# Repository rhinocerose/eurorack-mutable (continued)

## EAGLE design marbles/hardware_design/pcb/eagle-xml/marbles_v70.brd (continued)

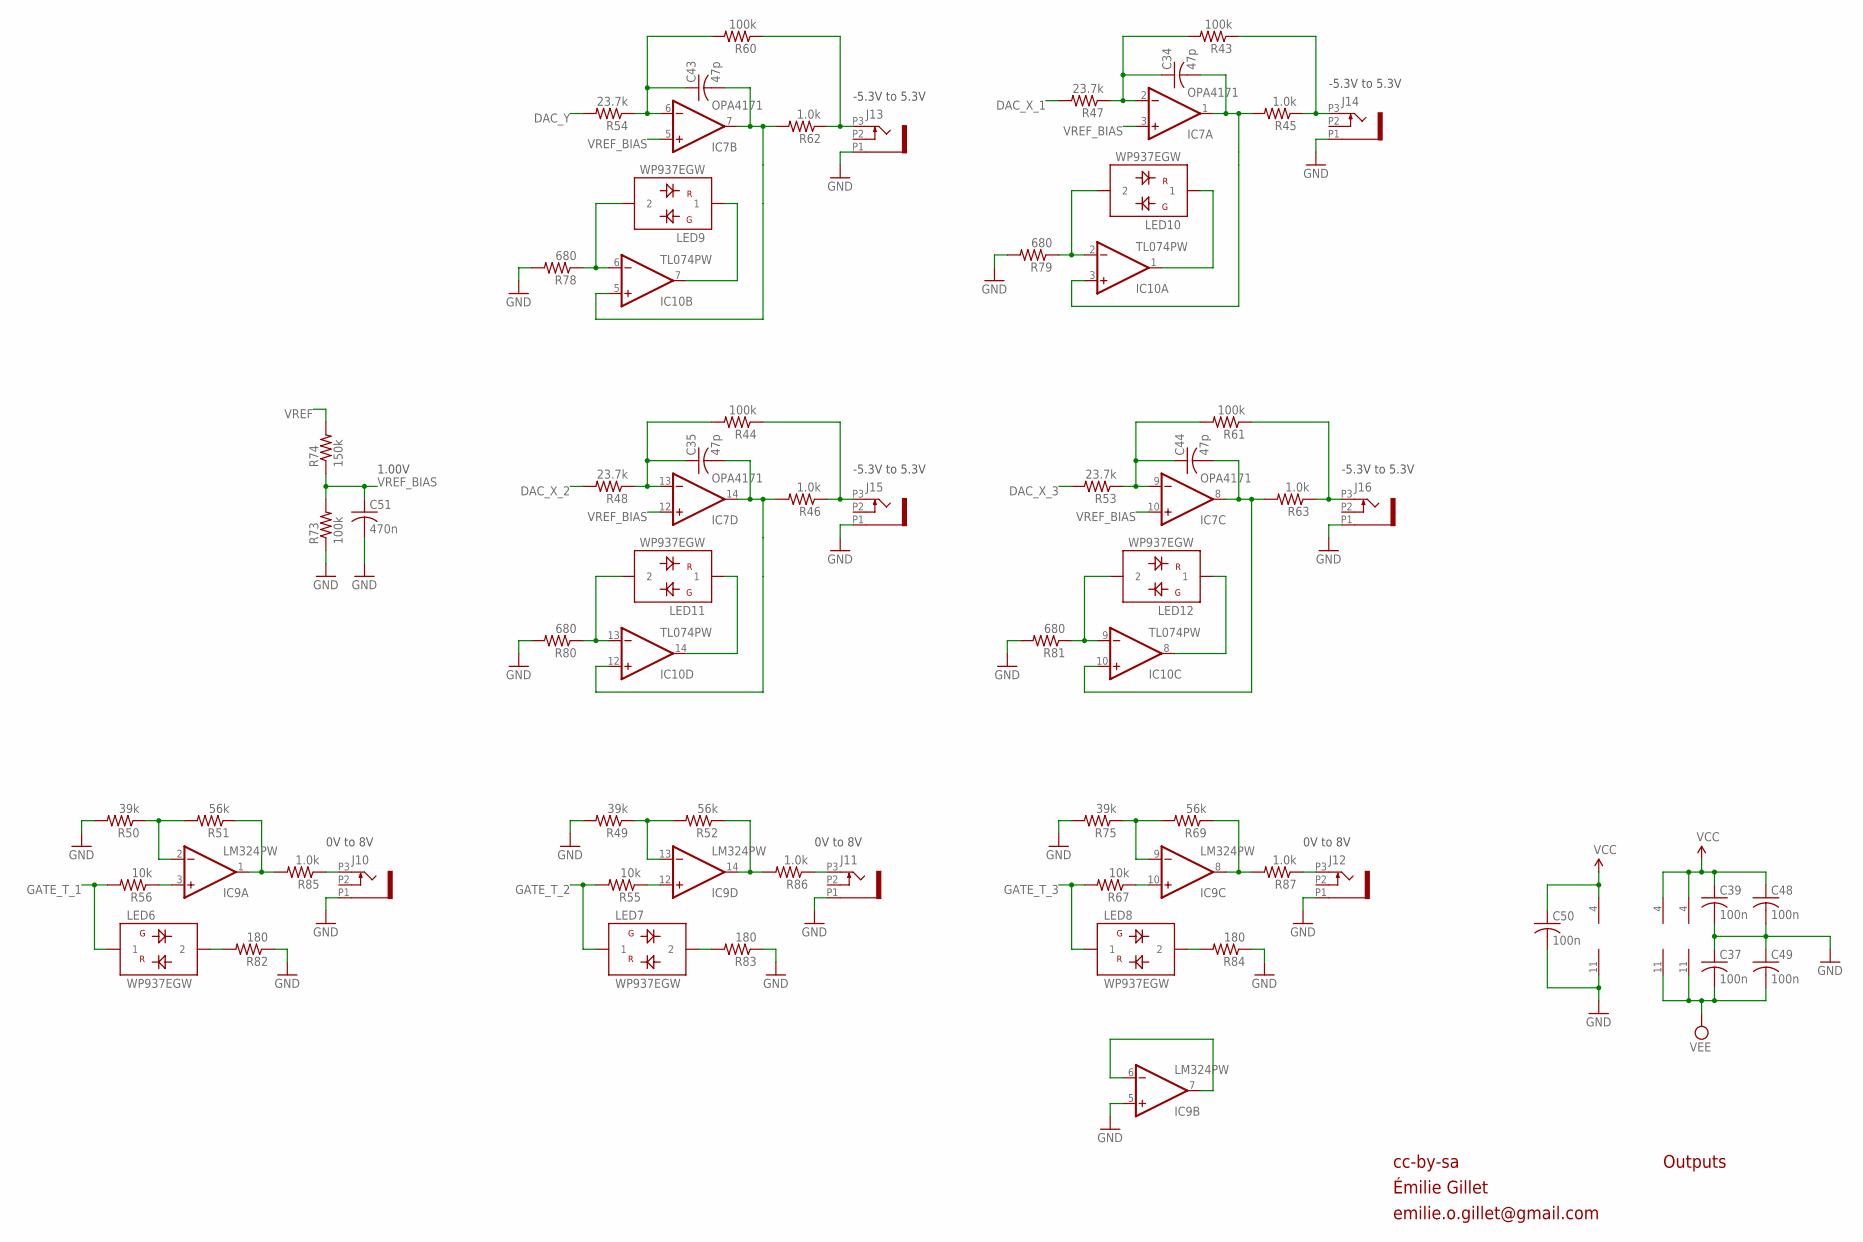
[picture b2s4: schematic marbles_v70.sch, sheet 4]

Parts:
C34, C35, C43, C44: 47p; C0402
C37, C39, C48, C49, C50: 100n; C0402
C51: 470n; C0402
IC7: OPA4171; TSSOP14_065
IC9: LM324PW; TSSOP14_065
IC10: TL074PW; TSSOP14_065
J10, J11, J12, J13, J14, J15, J16: PJ301_THONKICONN6; WQP_PJ_301M6
LED6, LED7, LED8, LED9, LED10, LED11, LED12: WP937EGW; LED3MM
R43, R44, R60, R61, R73: 100k; R0402
R45, R46, R62, R63, R85, R86, R87: 1.0k; R0603
R47, R48, R53, R54: 23.7k; R0402
R49, R50, R75: 39k; R0402
R51, R52, R69: 56k; R0402
R55, R56, R67: 10k; R0402
R74: 150k; R0402
R78, R79, R80, R81: 680; R0402
R82, R83, R84: 180; R0402

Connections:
DAC_X_1: R47.2; also elsewhere on the board
DAC_X_2: R48.2; also elsewhere on the board
DAC_X_3: R53.2; also elsewhere on the board
DAC_Y: R54.2; also elsewhere on the board
GATE_T_1: LED6.1, R56.2; also elsewhere on the board
GATE_T_2: LED7.1, R55.2; also elsewhere on the board
GATE_T_3: LED8.1, R67.2; also elsewhere on the board
GND: C37.1, C39.2, C48.2, C49.1, C50.2, C51.2, IC9.5 (+IN), IC9.11 (V-), J10.P1 (1), J11.P1 (1), J12.P1 (1), J13.P1 (1), J14.P1 (1), J15.P1 (1), J16.P1 (1), R49.2, R50.2, R73.1, R75.2, R78.2, R79.2, R80.2, R81.2, R82.1, R83.1, R84.1; also elsewhere on the board
unnamed: IC9.12 (+IN), R55.1
unnamed: IC9.1 (OUT), R51.1, R85.2
unnamed: J10.P3 (3), R85.1
unnamed: IC9.2 (-IN), R50.1, R51.2
unnamed: LED6.2, R82.2
unnamed: IC9.3 (+IN), R56.1
unnamed: IC9.6 (-IN), IC9.7 (OUT)
unnamed: IC9.14 (OUT), R52.1, R86.2
unnamed: IC9.13 (-IN), R49.1, R52.2
unnamed: IC9.10 (+IN), R67.1
unnamed: IC9.8 (OUT), R69.1, R87.2
unnamed: J11.P3 (3), R86.1
unnamed: J12.P3 (3), R87.1
unnamed: IC9.9 (-IN), R69.2, R75.1
unnamed: LED7.2, R83.2
unnamed: C43.2, IC7.7 (OUT), IC10.5 (+IN), R62.2
unnamed: LED8.2, R84.2
unnamed: J15.P3 (3), R44.1, R46.1
unnamed: J13.P3 (3), R60.1, R62.1
unnamed: C35.1, IC7.13 (-IN), R44.2, R48.1
unnamed: J16.P3 (3), R61.1, R63.1
unnamed: C44.1, IC7.9 (-IN), R53.1, R61.2
unnamed: C34.1, IC7.2 (-IN), R43.2, R47.1
unnamed: C43.1, IC7.6 (-IN), R54.1, R60.2
unnamed: J14.P3 (3), R43.1, R45.1
unnamed: IC10.6 (-IN), LED9.2, R78.1
unnamed: IC10.7 (OUT), LED9.1
unnamed: C34.2, IC7.1 (OUT), IC10.3 (+IN), R45.2
unnamed: IC10.2 (-IN), LED10.2, R79.1
unnamed: IC10.1 (OUT), LED10.1
unnamed: C35.2, IC7.14 (OUT), IC10.12 (+IN), R46.2
unnamed: IC10.13 (-IN), LED11.2, R80.1
unnamed: IC10.14 (OUT), LED11.1
unnamed: C44.2, IC7.8 (OUT), IC10.10 (+IN), R63.2
unnamed: IC10.9 (-IN), LED12.2, R81.1
unnamed: IC10.8 (OUT), LED12.1
VCC: C39.1, C48.1, C50.1, IC7.4 (V+), IC9.4 (V+), IC10.4 (V+); also elsewhere on the board
VEE: C37.2, C49.2, IC7.11 (V-), IC10.11 (V-); also elsewhere on the board
VREF: R74.2; also elsewhere on the board
VREF_BIAS: C51.1, IC7.3 (+IN), IC7.5 (+IN), IC7.10 (+IN), IC7.12 (+IN), R73.2, R74.1

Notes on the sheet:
-5.3V to 5.3V
0V to 8V
cc-by-sa
Outputs
1.00V
Émilie Gillet
emilie.o.gillet@gmail.com

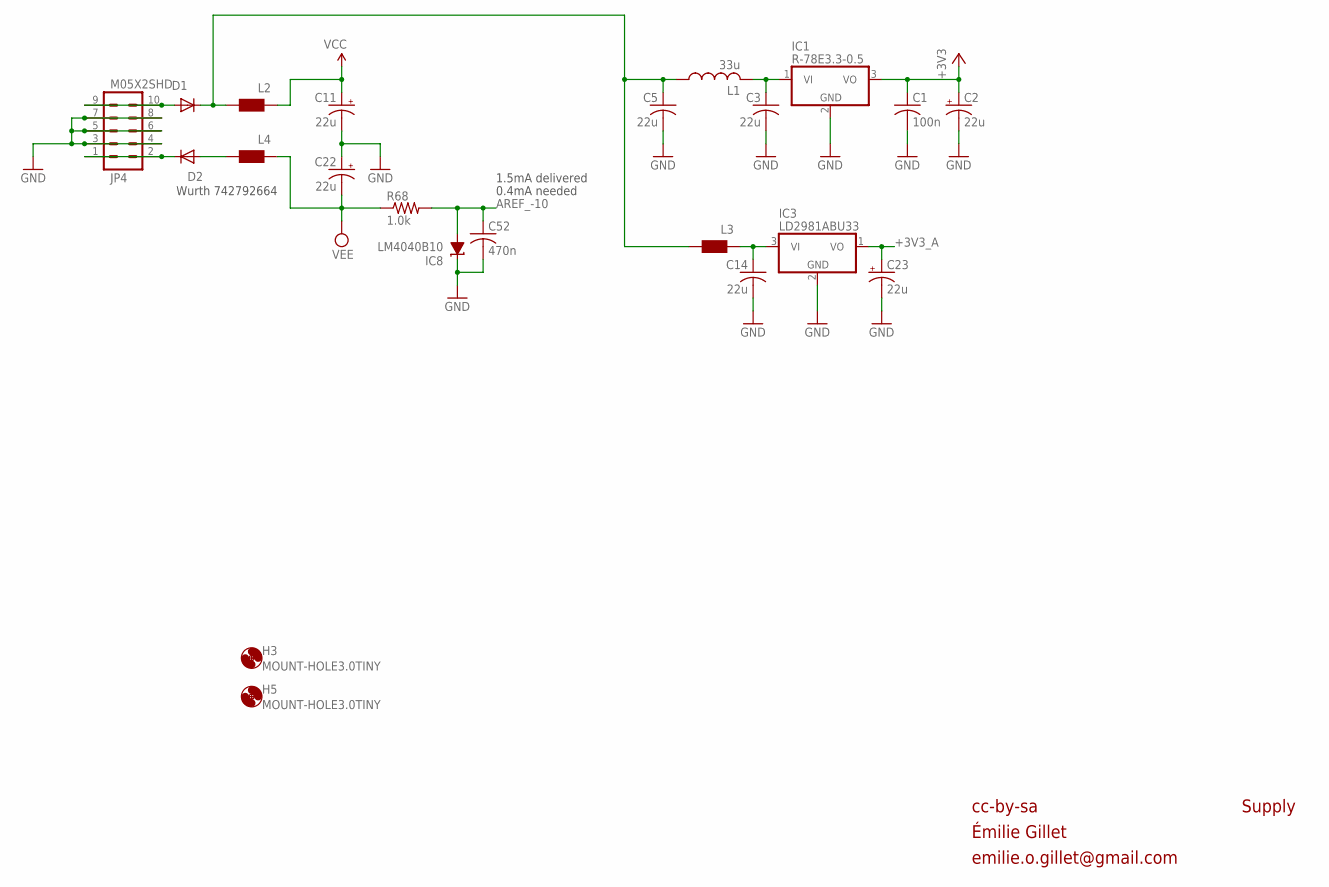
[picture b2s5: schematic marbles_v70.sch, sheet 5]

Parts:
C1: 100n; C0402
C2, C11, C22, C23: 22u; PANASONIC_C
C3, C5, C14: 22u; C1206
C52: 470n; C0402
D1, D2: 1N5819HW; SOD123
H3, H5: MOUNT-HOLE3.0TINY; 3,0TINY
IC1: R-78E3.3-0.5; WE78
IC3: LD2981ABU33; SOT89
IC8: LM4040B10; DBZ_R-PDSO-G3
JP4: M05X2SHD; 2X5-SHROUDED
L1: 33u; L2012C
L2, L3, L4: WE-CBF_0603; 0603
R68: 1.0k; R0402

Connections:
+3V3: C1.1, C2.+, IC1.3 (VO); also elsewhere on the board
+3V3_A: C23.+, IC3.1 (VO); also elsewhere on the board
AREF_-10: C52.1, IC8.2 (A), R68.2; also elsewhere on the board
GND: C1.2, C2.-, C3.2, C5.2, C11.-, C14.2, C22.+, C23.-, C52.2, IC1.2 (GND), IC3.2 (GND), IC8.1 (C), JP4.3, JP4.4, JP4.5, JP4.6, JP4.7, JP4.8; also elsewhere on the board
unnamed: C14.1, IC3.3 (VI), L3.1
unnamed: C5.1, D1.C, L1.1, L2.2, L3.2
unnamed: D2.A, L4.2
unnamed: C3.1, IC1.1 (VI), L1.2
unnamed: D1.A, JP4.9, JP4.10
unnamed: D2.C, JP4.1, JP4.2
VCC: C11.+, L2.1; also elsewhere on the board
VEE: C22.-, L4.1, R68.1; also elsewhere on the board

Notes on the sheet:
0.4mA needed
cc-by-sa
Supply
Wurth 742792664
1.5mA delivered
Émilie Gillet
emilie.o.gillet@gmail.com

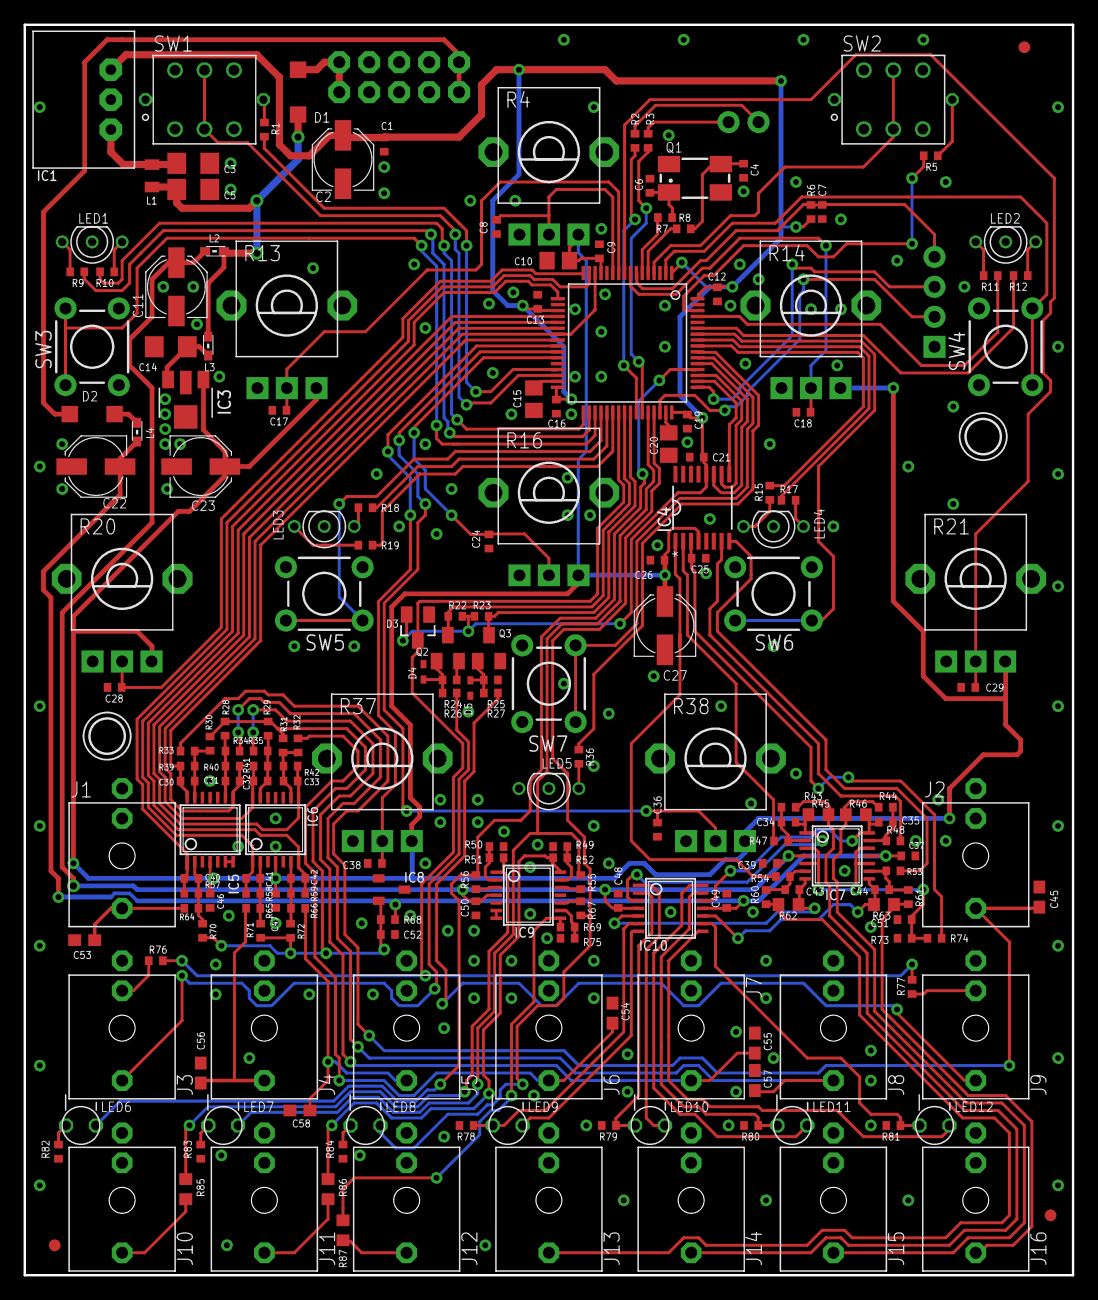
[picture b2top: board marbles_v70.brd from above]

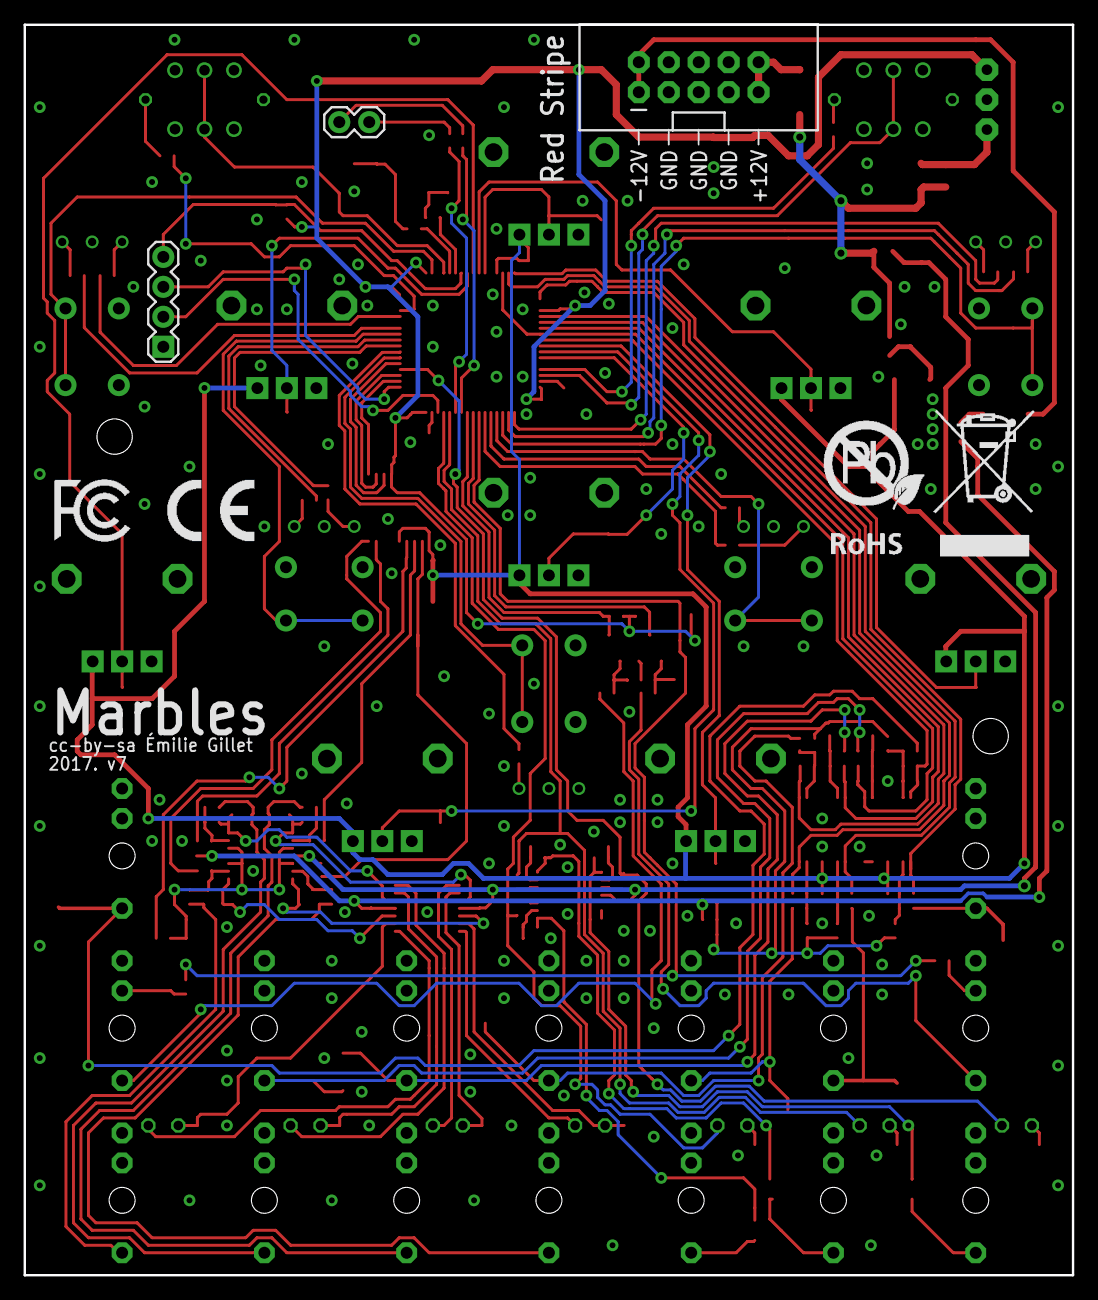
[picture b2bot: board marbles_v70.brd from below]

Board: 2 copper layers, 88.9 x 106.0 mm, 213 parts (6 on the bottom side), 141 nets.

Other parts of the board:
U$2: ROHS_BIG
U$4: CE_MEDIUM
U$5: FCC_MEDIUM

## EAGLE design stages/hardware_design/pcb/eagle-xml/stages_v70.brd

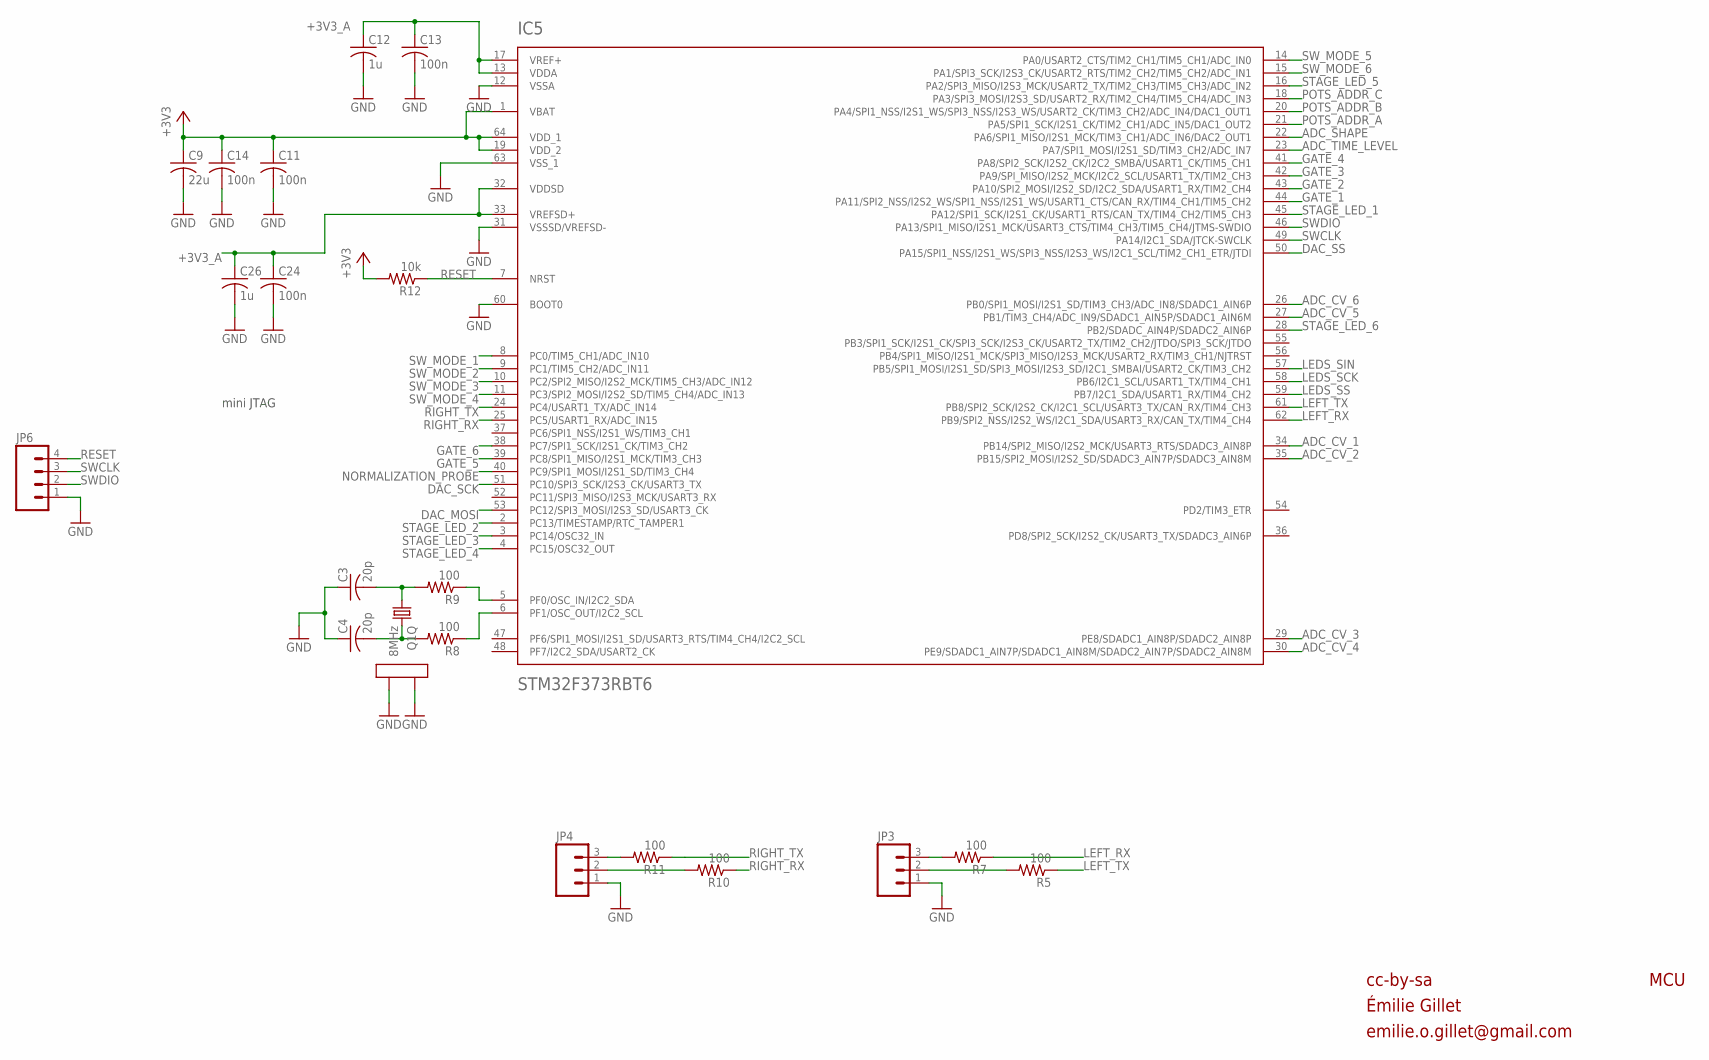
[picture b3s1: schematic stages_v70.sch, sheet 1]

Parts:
C3, C4: 20p; C0402
C9: 22u; C1206
C11, C13, C14, C24: 100n; C0402
C12, C26: 1u; C0402
IC5: STM32F373RBT6; TQFP-10X10-64
JP3, JP4: M03PTH; 1X03
JP6: M04PTH; 1X04
Q1: 8MHz; CTS406
R5, R7, R8, R9, R10, R11: 100; R0402
R12: 10k; R0402

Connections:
+3V3: C9.1, C11.1, C14.1, IC5.1 (VBAT), IC5.19 (VDD_2), IC5.64 (VDD_1), R12.2; also elsewhere on the board
+3V3_A: C12.1, C13.1, C24.1, C26.1, IC5.13 (VDDA), IC5.17 (VREF+), IC5.32 (VDDSD), IC5.33 (VREFSD+); also elsewhere on the board
ADC_CV_1: IC5.34 (PB14/SPI2_MISO/I2S2_MCK/USART3_RTS/SDAD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); also elsewhere on the board
ADC_CV_2: IC5.35 (PB15/SPI2_MOSI/I2S2_SD/SDADC3_AIN7P/SDA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); also elsewhere on the board
ADC_CV_3: IC5.29 (PE8/SDADC1_AIN8P/SDADC2_AIN8P); also elsewhere on the board
ADC_CV_4: IC5.30 (PE9/SDADC1_AIN7P/SDADC1_AIN8M/SDADC2_AI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); also elsewhere on the board
ADC_CV_5: IC5.27 (PB1/TIM3_CH4/ADC_IN9/SDADC1_AIN5P/SDADC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); also elsewhere on the board
ADC_CV_6: IC5.26 (PB0/SPI1_MOSI/I2S1_SD/TIM3_CH3/ADC_IN8/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); also elsewhere on the board
ADC_SHAPE: IC5.22 (PA6/SPI1_MISO/I2S1_MCK/TIM3_CH1/ADC_IN6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); also elsewhere on the board
ADC_TIME_LEVEL: IC5.23 (PA7/SPI1_MOSI/I2S1_SD/TIM3_CH2/ADC_IN7); also elsewhere on the board
DAC_MOSI: IC5.53 (PC12/SPI3_MOSI/I2S3_SD/USART3_CK); also elsewhere on the board
DAC_SCK: IC5.51 (PC10/SPI3_SCK/I2S3_CK/USART3_TX); also elsewhere on the board
DAC_SS: IC5.50 (PA15/SPI1_NSS/I2S1_WS/SPI3_NSS/I2S3_WS/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); also elsewhere on the board
GATE_1: IC5.44 (PA11/SPI2_NSS/I2S2_WS/SPI1_NSS/I2S1_WS/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); also elsewhere on the board
GATE_2: IC5.43 (PA10/SPI2_MOSI/I2S2_SD/I2C2_SDA/USART1_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); also elsewhere on the board
GATE_3: IC5.42 (PA9/SPI_MISO/I2S2_MCK/I2C2_SCL/USART1_T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); also elsewhere on the board
GATE_4: IC5.41 (PA8/SPI2_SCK/I2S2_CK/I2C2_SMBA/USART1_C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); also elsewhere on the board
GATE_5: IC5.39 (PC8/SPI1_MISO/I2S1_MCK/TIM3_CH3); also elsewhere on the board
GATE_6: IC5.38 (PC7/SPI1_SCK/I2S1_CK/TIM3_CH2); also elsewhere on the board
GND: C3.1, C4.1, C9.2, C11.2, C12.2, C13.2, C14.2, C24.2, C26.2, IC5.12 (VSSA), IC5.31 (VSSSD/VREFSD-), IC5.60 (BOOT0), IC5.63 (VSS_1), JP3.1, JP4.1, JP6.1, Q1.2 (LID1), Q1.4 (LID2); also elsewhere on the board
LEDS_SCK: IC5.58 (PB6/I2C1_SCL/USART1_TX/TIM4_CH1); also elsewhere on the board
LEDS_SIN: IC5.57 (PB5/SPI1_MOSI/I2S1_SD/SPI3_MOSI/I2S3_SD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); also elsewhere on the board
LEDS_SS: IC5.59 (PB7/I2C1_SDA/USART1_RX/TIM4_CH2); also elsewhere on the board
LEFT_RX: IC5.62 (PB9/SPI2_NSS/I2S2_WS/I2C1_SDA/USART3_RX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), R7.1
LEFT_RX_R: JP3.3, R7.2
LEFT_TX: IC5.61 (PB8/SPI2_SCK/I2S2_CK/I2C1_SCL/USART3_TX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), R5.1
LEFT_TX_R: JP3.2, R5.2
unnamed: C3.2, Q1.1, R9.2
unnamed: C4.2, Q1.3 (2), R8.2
unnamed: IC5.5 (PF0/OSC_IN/I2C2_SDA), R9.1
unnamed: IC5.6 (PF1/OSC_OUT/I2C2_SCL), R8.1
NORMALIZATION_PROBE: IC5.40 (PC9/SPI1_MOSI/I2S1_SD/TIM3_CH4); also elsewhere on the board
POTS_ADDR_A: IC5.21 (PA5/SPI1_SCK/I2S1_CK/TIM2_CH1/ADC_IN5/D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); also elsewhere on the board
POTS_ADDR_B: IC5.20 (PA4/SPI1_NSS/I2S1_WS/SPI3_NSS/I2S3_WS/U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); also elsewhere on the board
POTS_ADDR_C: IC5.18 (PA3/SPI3_MOSI/I2S3_SD/USART2_RX/TIM2_CH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); also elsewhere on the board
RESET: IC5.7 (NRST), JP6.4, R12.1
RIGHT_RX: IC5.25 (PC5/USART1_RX/ADC_IN15), R10.1
RIGHT_RX_R: JP4.2, R10.2
RIGHT_TX: IC5.24 (PC4/USART1_TX/ADC_IN14), R11.1
RIGHT_TX_R: JP4.3, R11.2
STAGE_LED_1: IC5.45 (PA12/SPI1_SCK/I2S1_CK/USART1_RTS/CAN_TX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); also elsewhere on the board
STAGE_LED_2: IC5.2 (PC13/TIMESTAMP/RTC_TAMPER1); also elsewhere on the board
STAGE_LED_3: IC5.3 (PC14/OSC32_IN); also elsewhere on the board
STAGE_LED_4: IC5.4 (PC15/OSC32_OUT); also elsewhere on the board
STAGE_LED_5: IC5.16 (PA2/SPI3_MISO/I2S3_MCK/USART2_TX/TIM2_C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); also elsewhere on the board
STAGE_LED_6: IC5.28 (PB2/SDADC_AIN4P/SDADC2_AIN6P); also elsewhere on the board
SWCLK: IC5.49 (PA14/I2C1_SDA/JTCK-SWCLK), JP6.3
SWDIO: IC5.46 (PA13/SPI1_MISO/I2S1_MCK/USART3_CTS/TIM4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), JP6.2
SW_MODE_1: IC5.8 (PC0/TIM5_CH1/ADC_IN10); also elsewhere on the board
SW_MODE_2: IC5.9 (PC1/TIM5_CH2/ADC_IN11); also elsewhere on the board
SW_MODE_3: IC5.10 (PC2/SPI2_MISO/I2S2_MCK/TIM5_CH3/ADC_IN12); also elsewhere on the board
SW_MODE_4: IC5.11 (PC3/SPI2_MOSI/I2S2_SD/TIM5_CH4/ADC_IN13); also elsewhere on the board
SW_MODE_5: IC5.14 (PA0/USART2_CTS/TIM2_CH1/TIM5_CH1/ADC_IN0); also elsewhere on the board
SW_MODE_6: IC5.15 (PA1/SPI3_SCK/I2S3_CK/USART2_RTS/TIM2_CH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); also elsewhere on the board

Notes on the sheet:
cc-by-sa
MCU
mini JTAG
Émilie Gillet
emilie.o.gillet@gmail.com

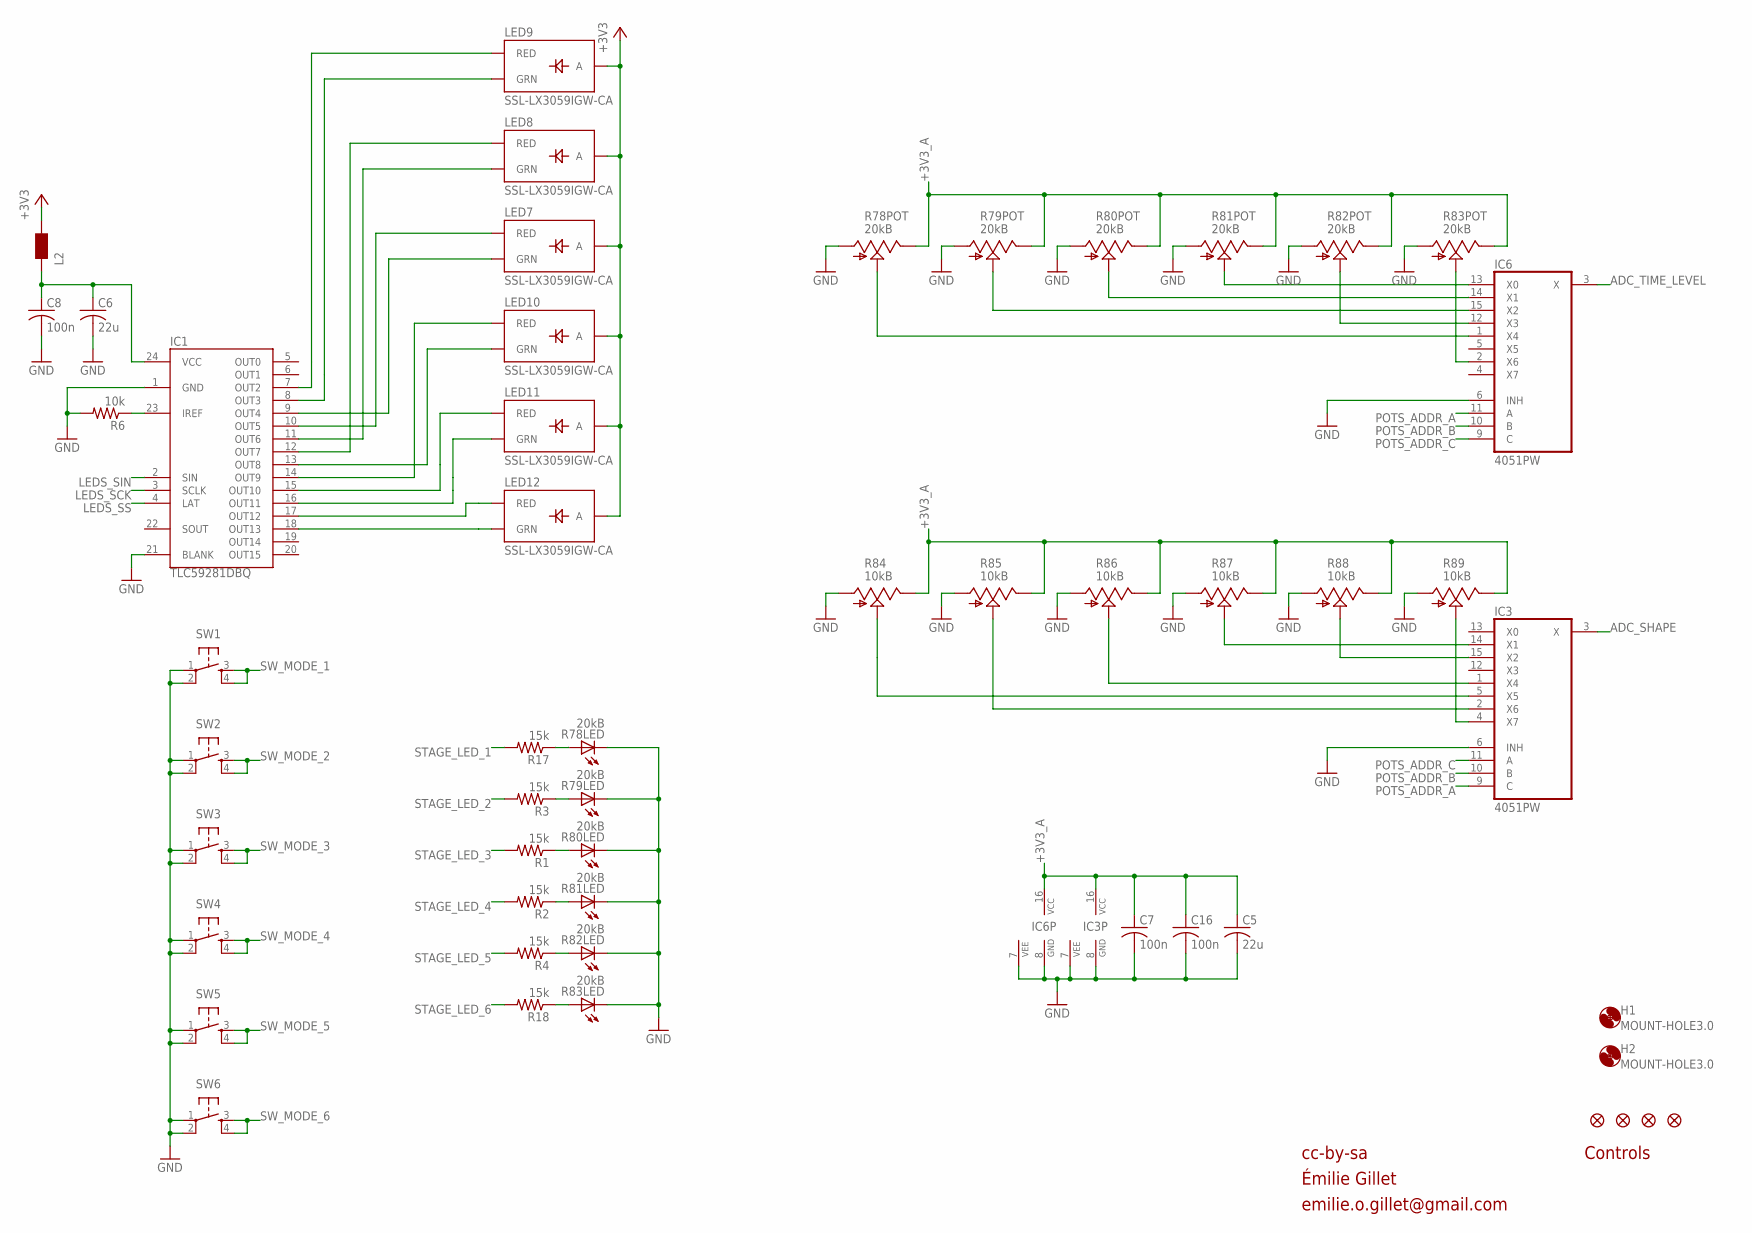
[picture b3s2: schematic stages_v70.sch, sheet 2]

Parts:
C5, C6: 22u; C1206
C7, C8, C16: 100n; C0402
H1, H2: MOUNT-HOLE3.0; 3,0
IC1: TLC59281DBQ; TSSOP24_0635
IC3, IC6: 4051PW; TSSOP16_065
JP1, JP2, JP7, JP8: FIDUCIAL1X2; FIDUCIAL-1X2
L2: WE-CBF_0603; 0603
LED7, LED8, LED9, LED10, LED11, LED12: SSL-LX3059IGW-CA; LED-BICOLOR-THROUGHHOLE-LUMEX
R1, R2, R3, R4, R17, R18: 15k; R0402
R6: 10k; R0402
R78, R79, R80, R81, R82, R83: 20kB; BOURNS_SLIDER
R84, R85, R86, R87, R88, R89: 10kB; ALPS_POT_NARROW
SW1, SW2, SW3, SW4, SW5, SW6: TAC_SWITCHPTH; TACTILE-PTH

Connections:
+3V3: L2.2, LED7.A, LED8.A, LED9.A, LED10.A, LED11.A, LED12.A; also elsewhere on the board
+3V3_A: C5.1, C7.1, C16.1, IC3.16 (VCC), IC6.16 (VCC), R78.3 (E), R79.3 (E), R80.3 (E), R81.3 (E), R82.3 (E), R83.3 (E), R84.P$1 (E), R85.P$1 (E), R86.P$1 (E), R87.P$1 (E), R88.P$1 (E), R89.P$1 (E); also elsewhere on the board
ADC_SHAPE: IC3.3 (X); also elsewhere on the board
ADC_TIME_LEVEL: IC6.3 (X); also elsewhere on the board
GND: C5.2, C6.2, C7.2, C8.2, C16.2, IC1.1 (GND), IC1.21 (BLANK), IC3.6 (INH), IC3.7 (VEE), IC3.8 (GND), IC6.6 (INH), IC6.7 (VEE), IC6.8 (GND), R6.2, R78.1 (A), R78.E (C), R79.1 (A), R79.E (C), R80.1 (A), R80.E (C), R81.1 (A), R81.E (C), R82.1 (A), R82.E (C), R83.1 (A), R83.E (C), R84.P$3 (A), R85.P$3 (A), R86.P$3 (A), R87.P$3 (A), R88.P$3 (A), R89.P$3 (A), SW1.1, SW1.2, SW2.1, SW2.2, SW3.1, SW3.2, SW4.1, SW4.2, SW5.1, SW5.2, SW6.1, SW6.2; also elsewhere on the board
LEDS_SCK: IC1.3 (SCLK); also elsewhere on the board
LEDS_SIN: IC1.2 (SIN); also elsewhere on the board
LEDS_SS: IC1.4 (LAT); also elsewhere on the board
unnamed: IC1.10 (OUT5), LED7.RED_C (RED)
unnamed: IC1.18 (OUT13), LED12.GREEN_C (GRN)
unnamed: IC1.12 (OUT7), LED8.RED_C (RED)
unnamed: IC1.7 (OUT2), LED9.RED_C (RED)
unnamed: IC1.8 (OUT3), LED9.GREEN_C (GRN)
unnamed: IC1.13 (OUT8), LED10.GREEN_C (GRN)
unnamed: IC1.15 (OUT10), LED11.RED_C (RED)
unnamed: R17.1, R78.B (A)
unnamed: IC1.16 (OUT11), LED11.GREEN_C (GRN)
unnamed: IC1.17 (OUT12), LED12.RED_C (RED)
unnamed: IC1.11 (OUT6), LED8.GREEN_C (GRN)
unnamed: C6.1, C8.1, IC1.24 (VCC), L2.1
unnamed: IC1.14 (OUT9), LED10.RED_C (RED)
unnamed: IC6.1 (X4), R78.2 (S)
unnamed: R18.1, R83.B (A)
unnamed: IC6.2 (X6), R83.2 (S)
unnamed: IC6.12 (X3), R82.2 (S)
unnamed: IC6.13 (X0), R81.2 (S)
unnamed: IC6.14 (X1), R80.2 (S)
unnamed: IC6.15 (X2), R79.2 (S)
unnamed: IC3.2 (X6), R85.P$2 (S)
unnamed: IC3.4 (X7), R89.P$2 (S)
unnamed: IC3.1 (X4), R86.P$2 (S)
unnamed: IC3.14 (X1), R87.P$2 (S)
unnamed: IC3.15 (X2), R88.P$2 (S)
unnamed: IC3.5 (X5), R84.P$2 (S)
unnamed: R4.1, R82.B (A)
unnamed: IC1.23 (IREF), R6.1
unnamed: R2.1, R81.B (A)
unnamed: IC1.9 (OUT4), LED7.GREEN_C (GRN)
unnamed: R1.1, R80.B (A)
unnamed: R3.1, R79.B (A)
POTS_ADDR_A: IC3.9 (C), IC6.11 (A); also elsewhere on the board
POTS_ADDR_B: IC3.10 (B), IC6.10 (B); also elsewhere on the board
POTS_ADDR_C: IC3.11 (A), IC6.9 (C); also elsewhere on the board
STAGE_LED_1: R17.2; also elsewhere on the board
STAGE_LED_2: R3.2; also elsewhere on the board
STAGE_LED_3: R1.2; also elsewhere on the board
STAGE_LED_4: R2.2; also elsewhere on the board
STAGE_LED_5: R4.2; also elsewhere on the board
STAGE_LED_6: R18.2; also elsewhere on the board
SW_MODE_1: SW1.3, SW1.4; also elsewhere on the board
SW_MODE_2: SW2.3, SW2.4; also elsewhere on the board
SW_MODE_3: SW3.3, SW3.4; also elsewhere on the board
SW_MODE_4: SW4.3, SW4.4; also elsewhere on the board
SW_MODE_5: SW5.3, SW5.4; also elsewhere on the board
SW_MODE_6: SW6.3, SW6.4; also elsewhere on the board

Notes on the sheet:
cc-by-sa
Controls
Émilie Gillet
emilie.o.gillet@gmail.com

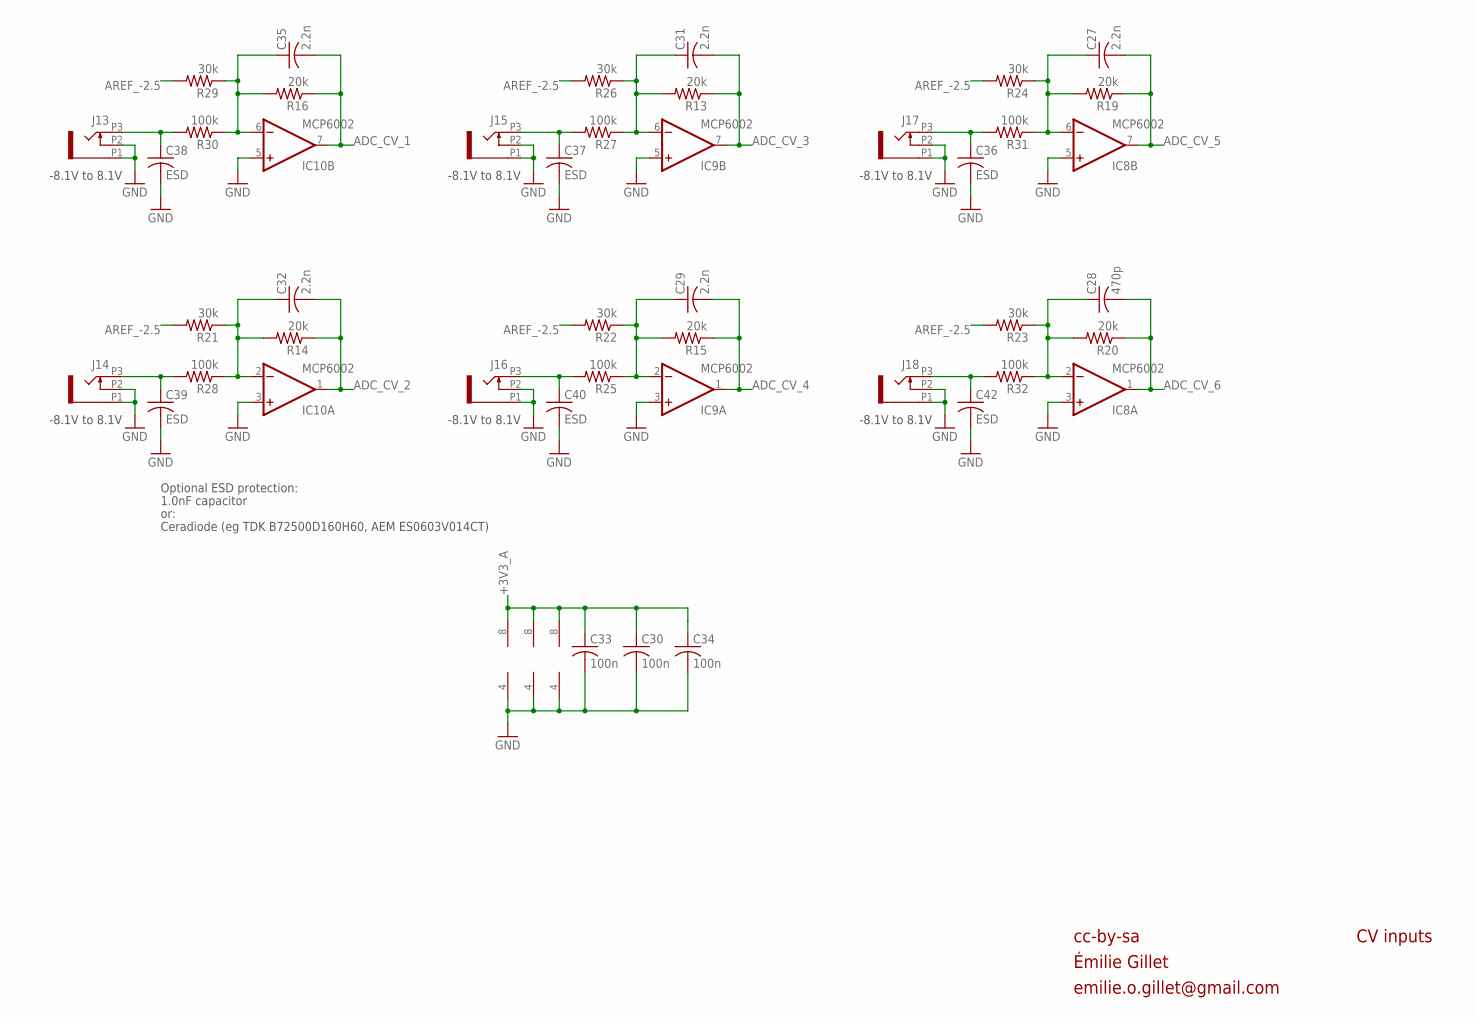
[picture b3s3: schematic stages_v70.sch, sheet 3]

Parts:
C27, C29, C31, C32, C35: 2.2n; C0402
C28: 470p; C0402
C30, C33, C34: 100n; C0402
C36, C37, C38, C39, C40, C42: ESD; C0603
IC8, IC9, IC10: MCP6002; MSOP-8
J13, J14, J15, J16, J17, J18: PJ301_THONKICONN6; WQP_PJ_301M6
R13, R14, R15, R16, R19, R20: 20k; R0402
R21, R22, R23, R24, R26, R29: 30k; R0402
R25, R27, R28, R30, R31, R32: 100k; R0402

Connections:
+3V3_A: C30.1, C33.1, C34.1, IC8.8 (V+), IC9.8 (V+), IC10.8 (V+); also elsewhere on the board
ADC_CV_1: C35.2, IC10.7 (OUT), R16.1; also elsewhere on the board
ADC_CV_2: C32.2, IC10.1 (OUT), R14.1; also elsewhere on the board
ADC_CV_3: C31.2, IC9.7 (OUT), R13.1; also elsewhere on the board
ADC_CV_4: C29.2, IC9.1 (OUT), R15.1; also elsewhere on the board
ADC_CV_5: C27.2, IC8.7 (OUT), R19.1; also elsewhere on the board
ADC_CV_6: C28.2, IC8.1 (OUT), R20.1; also elsewhere on the board
AREF_-2.5: R21.2, R22.2, R23.2, R24.2, R26.2, R29.2; also elsewhere on the board
GND: C30.2, C33.2, C34.2, C36.2, C37.2, C38.2, C39.2, C40.2, C42.2, IC8.3 (+IN), IC8.4 (V-), IC8.5 (+IN), IC9.3 (+IN), IC9.4 (V-), IC9.5 (+IN), IC10.3 (+IN), IC10.4 (V-), IC10.5 (+IN), J13.P1 (1), J13.P2 (2), J14.P1 (1), J14.P2 (2), J15.P1 (1), J15.P2 (2), J16.P1 (1), J16.P2 (2), J17.P1 (1), J17.P2 (2), J18.P1 (1), J18.P2 (2); also elsewhere on the board
MORPH_IN: C38.1, J13.P3 (3), R30.2
MORPH_IN1: C39.1, J14.P3 (3), R28.2
MORPH_IN2: C37.1, J15.P3 (3), R27.2
MORPH_IN3: C40.1, J16.P3 (3), R25.2
MORPH_IN4: C36.1, J17.P3 (3), R31.2
MORPH_IN5: C42.1, J18.P3 (3), R32.2
unnamed: C35.1, IC10.6 (-IN), R16.2, R29.1, R30.1
unnamed: C32.1, IC10.2 (-IN), R14.2, R21.1, R28.1
unnamed: C31.1, IC9.6 (-IN), R13.2, R26.1, R27.1
unnamed: C29.1, IC9.2 (-IN), R15.2, R22.1, R25.1
unnamed: C27.1, IC8.6 (-IN), R19.2, R24.1, R31.1
unnamed: C28.1, IC8.2 (-IN), R20.2, R23.1, R32.1

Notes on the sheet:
cc-by-sa
CV inputs
-8.1V to 8.1V
Optional ESD protection:
1.0nF capacitor
or:
Ceradiode (eg TDK B72500D160H60, AEM ES0603V014CT)
Émilie Gillet
emilie.o.gillet@gmail.com
